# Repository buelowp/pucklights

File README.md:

# Remote Control Wireless Energizer Puck Lights

There are a new breed of low power LED puck lights available which make use of 433 Mhz radios 
for remote control. However, they currently do not integrate with any sort of Micro allowing 
for more accesible remote control.

This project connects to the provided remote and adds the ability to put a motion detector 
into the system which will turn the lights on or off based on movement and available ambient 
light. The idea is to use the puck lights remotely without having to run power for stair lights 
while achieving a viable benefit.

## What these are
https://www.lowes.com/pd/Energizer-Remote-Controlled-2-Pack-3-in-Battery-Puck-Light/1000268307

## The Plan
Basically, these are battery operated with a 433Mhz receiver, and a 12V remote that has two 
buttons, on and off. By powering the remote with a 12V source, and then regulating the power 
down to 5V for the micro, you can simply run two leads from NPN transistors to the two buttons 
to act as remote triggers. Add in a IR motion detector and a photocell, and you can remotely
trigger the lights on activity. Add in a micro that can easily receive events from the internet
and you can even turn the lights on or off from anywhere.

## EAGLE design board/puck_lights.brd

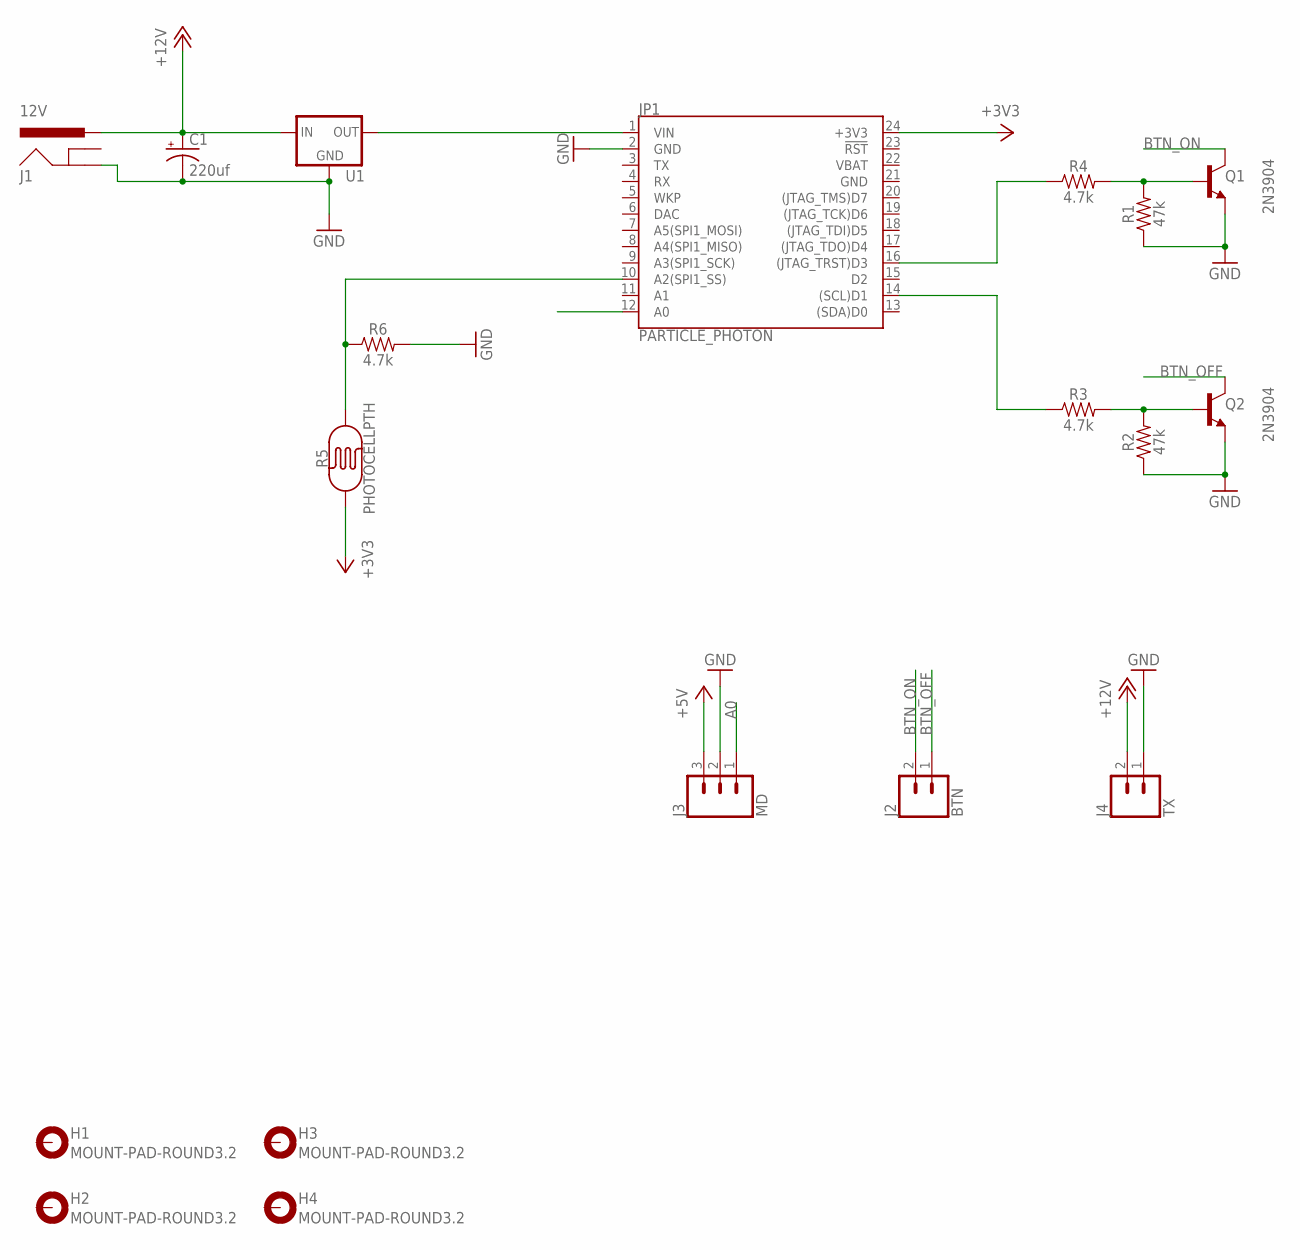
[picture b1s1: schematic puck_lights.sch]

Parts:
C1: 220uf; CPOL-RADIAL-2.5MM-6.5MM
H1, H2, H3, H4: MOUNT-PAD-ROUND3.2; 3,2-PAD
J1: 12V; POWER_JACK_SMD
J2: BTN; 1X02
J3: MD; JST-3-PTH
J4: TX; 1X02
JP1: PARTICLE_PHOTON
Q1, Q2: 2N3904; TO92
R1, R2: 47k; AXIAL-0.3
R3, R4, R6: 4.7k; AXIAL-0.3
R5: PHOTOCELLPTH; PHOTOCELL
U1: V_REG_78XX-TO-220; TO-220-ALT

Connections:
+3V3: JP1.24 (+3V3), R5.1
+5V: J3.3
+12V: C1.1 (+), J1.VIN0 (PWR), J4.2, U1.IN
A0: J3.1, JP1.12 (A0)
BTN_OFF: J2.1, Q2.1 (C)
BTN_ON: J2.2, Q1.1 (C)
GND: C1.2 (-), J1.P$4 (GND), J3.2, J4.1, JP1.2 (GND), JP1.21 (GND), Q1.3 (E), Q2.3 (E), R1.P$1 (1), R2.P$1 (1), R6.P$2 (2), U1.GND
unnamed: JP1.14 ((SCL)D1), R3.P$1 (1)
unnamed: JP1.1 (VIN), U1.OUT
unnamed: JP1.16 ((JTAG_TRST)D3), R4.P$1 (1)
unnamed: Q2.2 (B), R2.P$2 (2), R3.P$2 (2)
unnamed: Q1.2 (B), R1.P$2 (2), R4.P$2 (2)
unnamed: JP1.10 (A2(SPI1_SS)), R5.2, R6.P$1 (1)
VBAT: JP1.22 (VBAT)

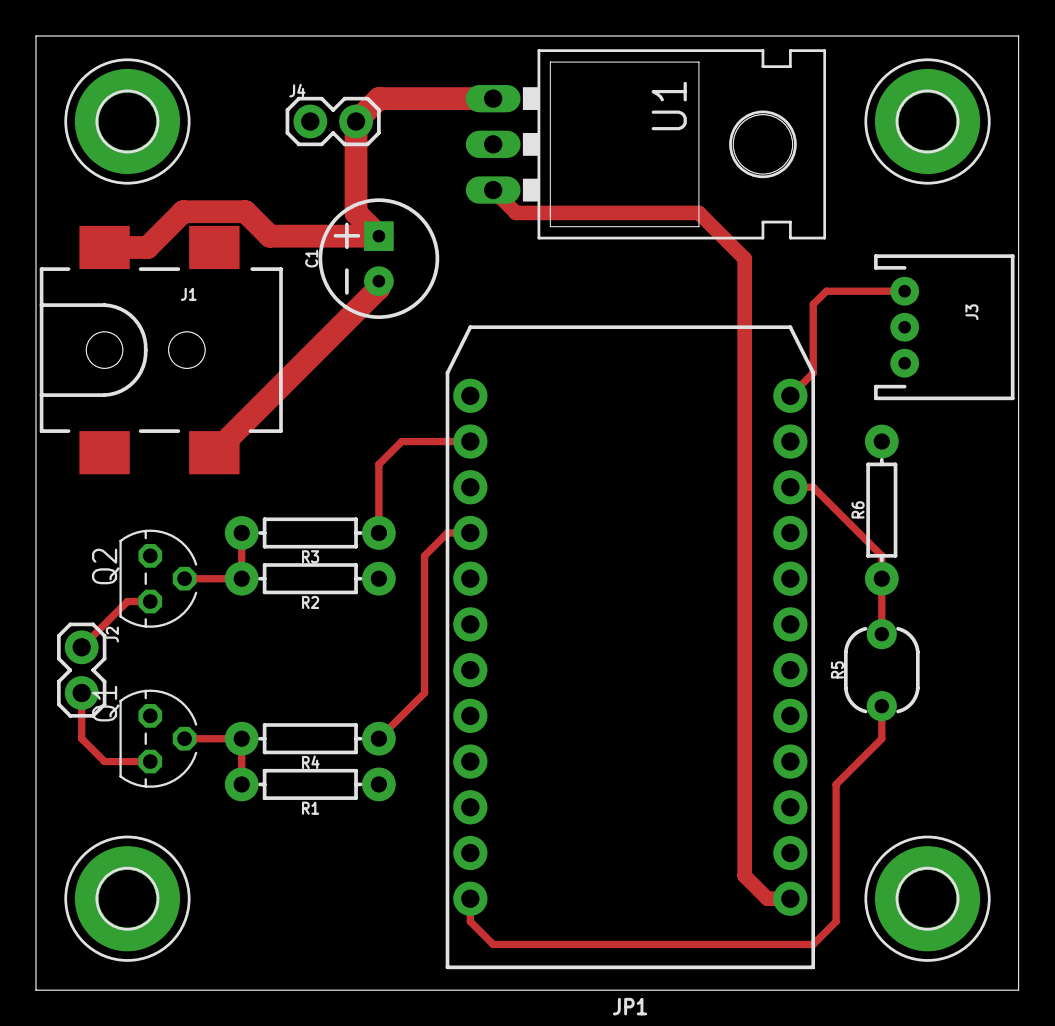
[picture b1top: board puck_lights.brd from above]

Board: 2 copper layers, 54.6 x 53.0 mm, 19 parts (0 on the bottom side), 12 nets.

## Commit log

2018-02-15 Adding content
2018-02-15 Adding remote functions to turn light on or off Fixing a few bugs
2018-02-15 Fixing a bug in how we read the photocell
2018-02-19 First working version
    * Adds a lockout to avoid instant retriggering
    * Adds a 1 minute warmup for the PIR
    * Sets light timeout to 5 minutes
2018-02-19 Time on improvement
    * If the lights are on, just restart the
    timeout so it's 5 minutes from the last movement.
2018-02-20 Turns out 800 is way too bright.
2018-05-12 Fixing up and installing
    * Fixed light sense value to be better for the actual hallway.
2018-05-13 Lowering light level again
2018-07-07 Updating to latest
2018-07-08 Some fixes
    Added function to set trigger value directly
    Dropped default to 25
    Made it possible to see last min value since reboot
2018-07-16 Lots of fixups
2019-08-10 Updates
    * Simplified the design
2019-12-21 Updates
    * Fixed it to not turn on during the day
    * Added Time support for that function
    * Shorted the time on period to 4 minutes
2021-01-04 fixes for issues with randomly turning on
2021-01-05 Fixups
    * Set lockout times to be sunrise/sunset, not a fixed time
    * Move some setup code around, and remove the 1 minute delay for a 1 second delay

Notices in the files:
parts and their libraries:
SparkFun-Capacitors: Licensing: Creative Commons ShareAlike 4.0 International - https://creativecommons.org/licenses/by-sa/4.0
